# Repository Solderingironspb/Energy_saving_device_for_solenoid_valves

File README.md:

# Energy_saving_device_for_solenoid_valves
### Энергосберегающее устройство для клапанов электромагнитных

# Смотреть видео:
## [YouTube](https://youtu.be/SwpbhSrmsd0?si=if_VcrNuy5G8k3mL)
## [RuTube](https://rutube.ru/video/6c48014d67a676c6d3780972b5abe38f/?r=wd)
## [Дзен](https://dzen.ru/video/watch/66ddffafeca9e1516de6e009?share_to=link)

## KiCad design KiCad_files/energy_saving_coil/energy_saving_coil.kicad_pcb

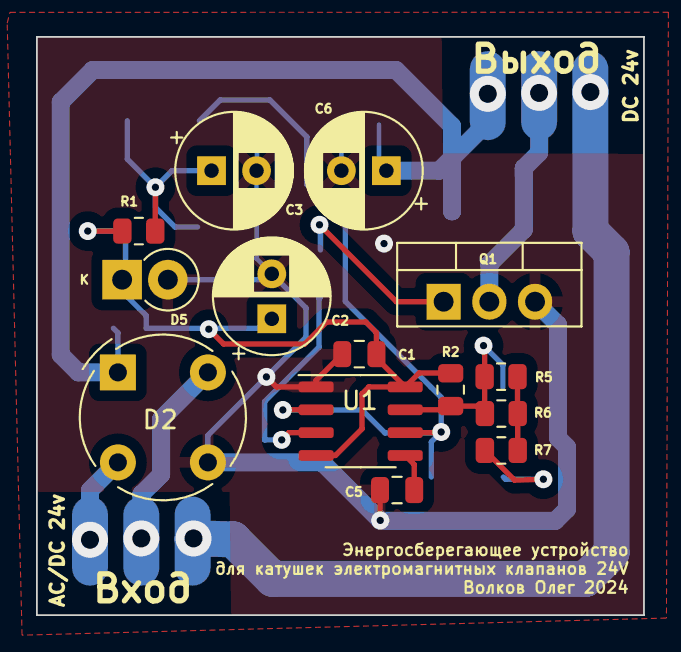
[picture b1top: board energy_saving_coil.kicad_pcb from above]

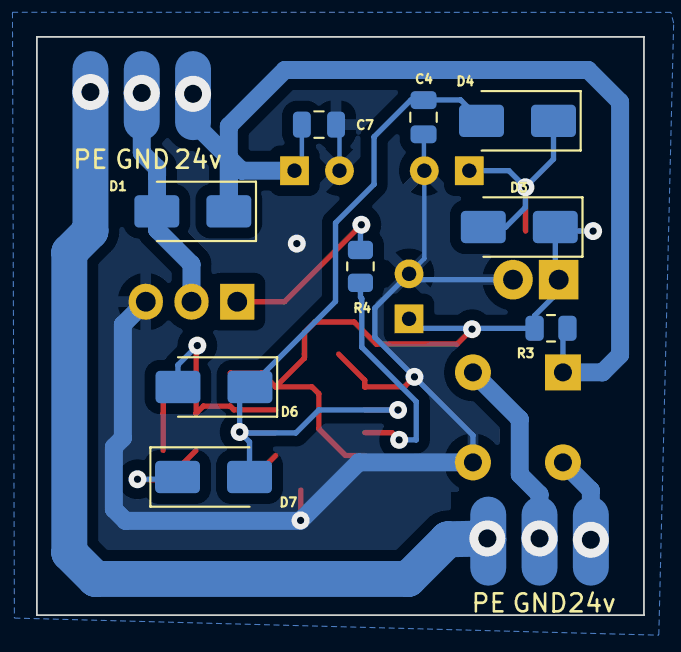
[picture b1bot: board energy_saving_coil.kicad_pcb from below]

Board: 2 copper layers, 33.7 x 32.1 mm, 23 parts (9 on the bottom side), 12 nets.

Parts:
C1, C5: 0.1uF; C_0805_2012Metric
C2: 22u 50v; CP_Radial_D6.3mm_P2.50mm
C3, C6: 47u 50v; CP_Radial_D6.3mm_P2.50mm
C4, C7: 0.068uF; C_0805_2012Metric
D1, D3, D4, D6, D7: M7; D_SMA
D2: 2W10; Diode_Bridge_Round_D9.0mm
D5: 12v 1N4742A; D_DO-41_SOD81_P2.54mm_Vertical_KathodeUp
Q1: IRFZ44N; TO-220-3_Vertical
R1, R2, R5, R6, R7: 100k; R_0805_2012Metric
R3: 2k; R_0805_2012Metric
R4: 1k; R_0805_2012Metric
U1: NE555D; SOIC-8_3.9x4.9mm_P1.27mm

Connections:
Coil_24v: C6.1, C7.2, D1.1 (K), D2.1 (+), R3.1
Coil_GND: D1.2 (A), Q1.2 (D)
GND: C1.2, C2.2, C3.2, C4.2, C5.2, C6.2, C7.1, D2.3 (-), D5.2 (A), Q1.3 (S), U1.1 (GND)
unnamed: C3.1, D3.2 (A), D4.1 (K), R1.2
unnamed: C1.1, C2.1, D3.1 (K), D5.1 (K), R1.1, R2.1, R3.2, U1.4 (R), U1.8 (VCC)
unnamed: C4.1, D4.2 (A), D6.1 (K), D7.2 (A), U1.2 (TR), U1.6 (THR)
unnamed: D6.2 (A), R2.2, R5.1, R6.1, U1.7 (DIS)
unnamed: D7.1 (K), R7.2
unnamed: Q1.1 (G), R4.2
unnamed: R5.2, R6.2, R7.1
unnamed: C5.1, U1.5 (CV)
unnamed: R4.1, U1.3 (Q)

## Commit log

2024-09-09 add files
